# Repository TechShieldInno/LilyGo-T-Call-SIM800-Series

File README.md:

# LilyGo-T-Call-SIM800-Series
This is a TTGO T-Call V1.4 ESP32 Wireless Module SIM Antenna SIM Card SIM800L Module Unsoldered

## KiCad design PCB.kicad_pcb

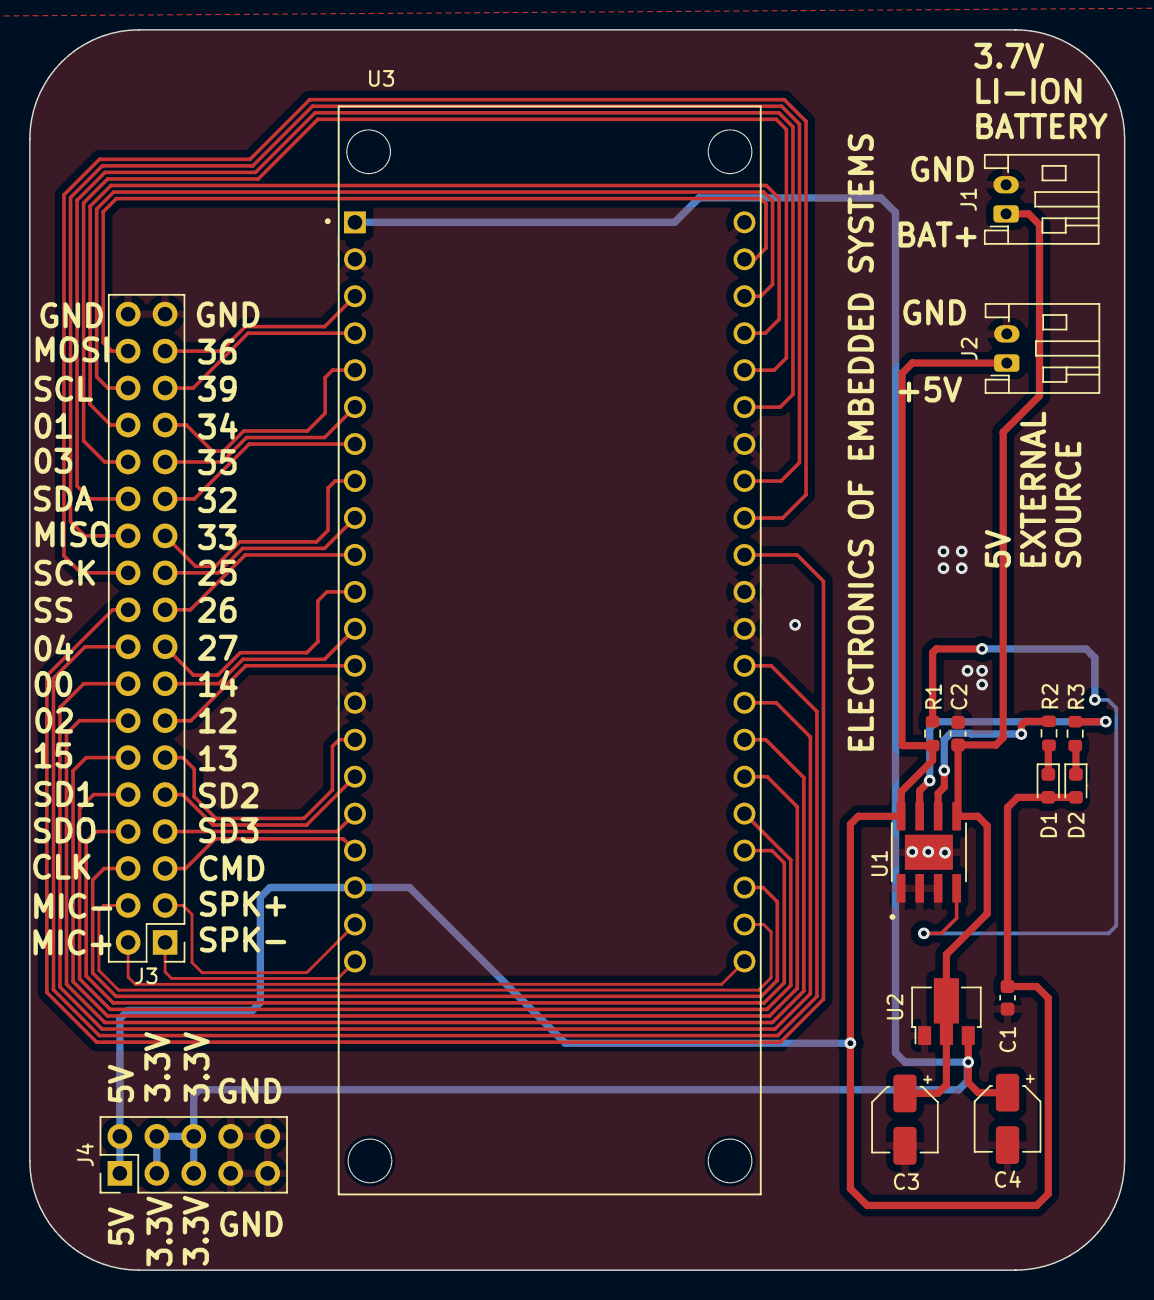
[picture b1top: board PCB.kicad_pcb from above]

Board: 2 copper layers, 75.2 x 85.2 mm, 16 parts (0 on the bottom side), 43 nets.

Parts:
C1, C2: 10U; C_0603_1608Metric
C3, C4: 1uF; CP_Elec_4x5.4
D1: GREEN; LED_0603_1608Metric
D2: RED; LED_0603_1608Metric
J1, J2: Li-IoN Bat; JST_PH_S2B-PH-K_1x02_P2.00mm_Horizontal
J3: Conn_01x36_Pin; PinHeader_2x18_P2.54mm_Vertical
J4: Conn_01x10_Pin; PinHeader_2x05_P2.54mm_Vertical
R1: 0.4; R_0603_1608Metric
R2, R3: 1K; R_0603_1608Metric
U1: TP4056
U2: MCP1700x-120xxMB; SOT-89-3
U3: LILYGO-T-CALL-SIM800L

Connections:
3.3V: C4.1, J4.3, J4.4, J4.5, J4.6, U2.3 (VO), U3.1 (3V3)
+5V: C1.1, D1.2 (A), D2.2 (A), J2.1, J4.1, J4.2, R1.1, U1.8 (CE), U3.19 (5V)
BAT: C2.1, C3.1, J1.1, U1.5 (BAT), U2.2 (VI)
CLK: J3.6, U3.24 (CLK)
CMD: J3.5, U3.18 (CMD)
GND: C1.2, C2.2, C3.2, C4.2, J1.2, J2.2, J3.35, J3.36, J4.7, J4.8, J4.9, J4.10, U1.1 (TEMP), U1.2 (PROG), U1.3 (GND), U1.9 (EP), U2.1 (GND), U3.2 (NC), U3.14 (GND), U3.31 (NC), U3.32 (NC), U3.36 (GND), U3.42 (GND)
GPIO0: J3.16, U3.29 (GPIO0)
GPIO1: J3.30, U3.39 (GPIO01/TXD)
GPIO2: J3.14, U3.28 (GPIO02)
GPIO3: J3.28, U3.38 (GPIO03/RXD)
GPIO4: J3.18, U3.30 (GPIO04)
GPIO12: J3.13, U3.13 (GPIO12)
GPIO13: J3.11, U3.15 (GPIO13)
GPIO14: J3.15, U3.12 (GPIO14)
GPIO15: J3.12, U3.27 (GPIO15)
GPIO25: J3.21, U3.9 (GPIO25)
GPIO26: J3.19, U3.10 (GPIO26)
GPIO27: J3.17, U3.11 (GPIO27)
GPIO32: J3.25, U3.7 (GPIO32)
GPIO33: J3.23, U3.8 (GPIO33)
GPIO34: J3.29, U3.5 (GPIO34)
GPIO35: J3.27, U3.6 (GPIO35)
GPIO36: J3.33, U3.3 (GPIO36/SVP)
GPIO39: J3.31, U3.4 (GPIO39/SVN)
MIC+: J3.2, U3.22 (MIC+)
MIC-: J3.4, U3.23 (MIC-)
MISO: J3.24, U3.35 (VSPI_MISO)
MOSI: J3.34, U3.41 (VSPI_MOSI)
unnamed: D1.1 (K), R2.1
unnamed: D2.1 (K), R3.1
unnamed: R1.2, U1.4 (VCC)
unnamed: R3.2, U1.7 (~CHRG)
unnamed: R2.2, U1.6 (~STDBY)
SCK: J3.22, U3.34 (VSPI_SCK)
SCL: J3.32, U3.40 (WIRE_SCL)
SD1: J3.10, U3.26 (SD1)
SD2: J3.9, U3.16 (SD2)
SD3: J3.7, U3.17 (SD3)
SDA: J3.26, U3.37 (WIRE_SDA)
SDO: J3.8, U3.25 (SD0)
SPK+: J3.3, U3.20 (SPK+)
SPK-: J3.1, U3.21 (SPK-)
SS: J3.20, U3.33 (VSPI_SS)
